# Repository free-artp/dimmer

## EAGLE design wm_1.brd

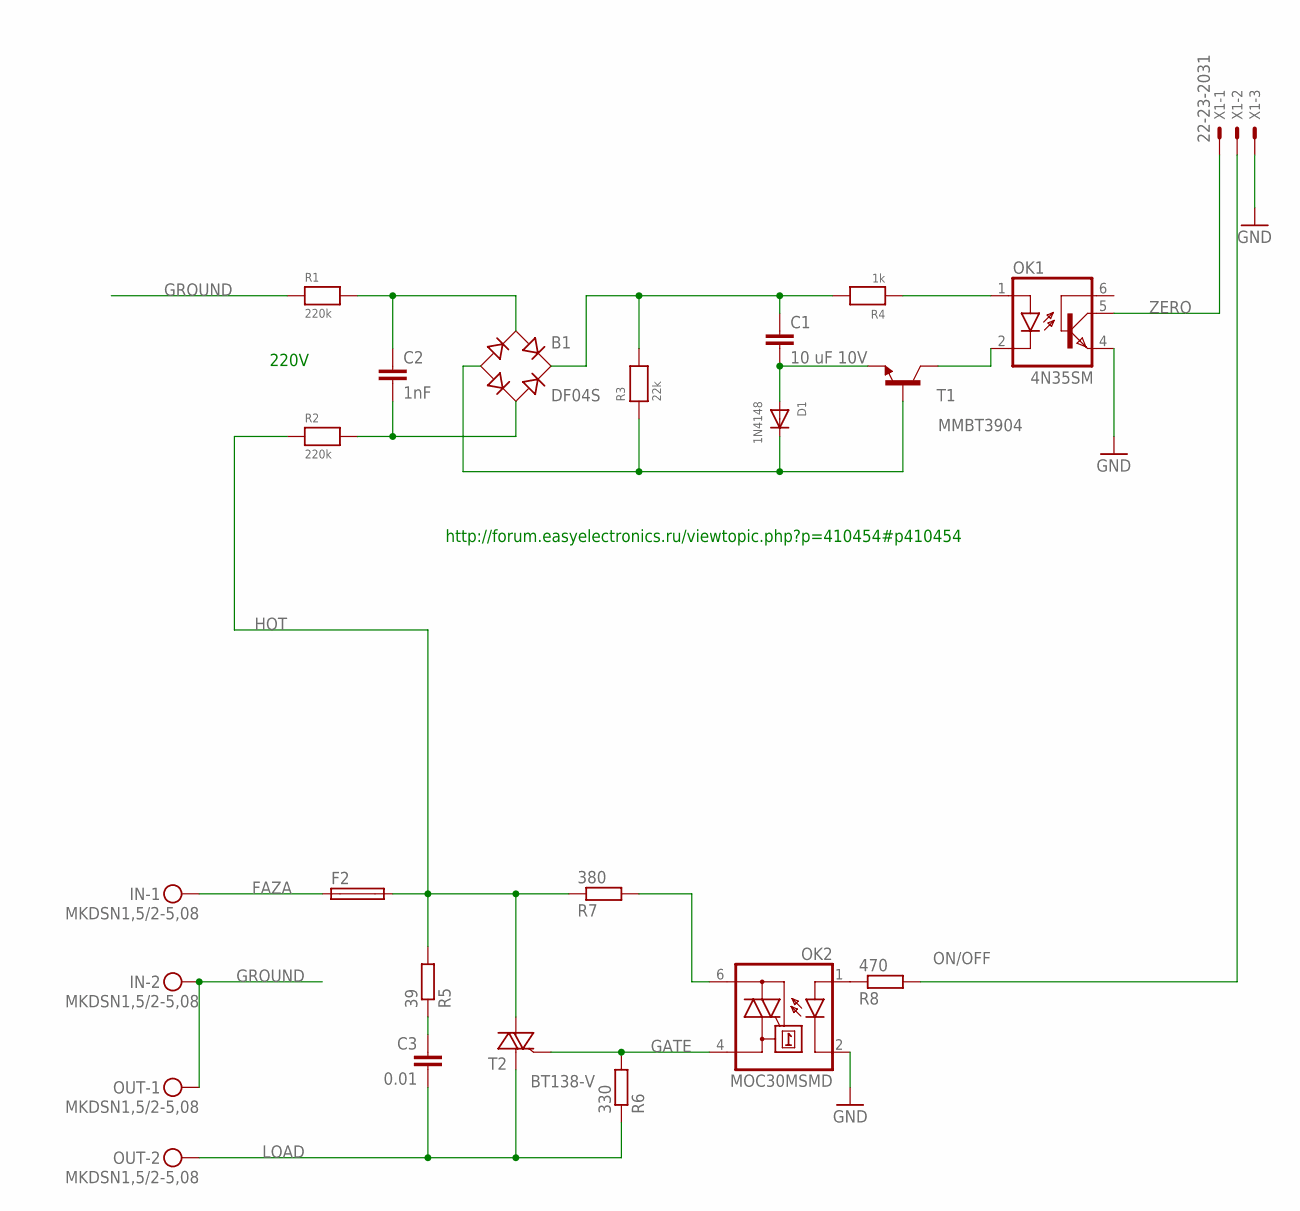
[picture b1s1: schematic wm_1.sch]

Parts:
B1: DF04S; DFS
C1: 10 uF 10V; C1206
C2: 1nF; C1206
C3: 0.01; C1206
D1: 1N4148; SOD-123
F2: SH22,5A
IN: MKDSN1,5/2-5,08
OK1: 4N35SM; DIL6-SMD
OK2: MOC30MSMD; DIL6-SMD
OUT: MKDSN1,5/2-5,08
R1, R2: 220k; 1206
R3: 22k; 1206
R4: 1k; 1206
R5: 39; R1206
R6: 330; R1206
R7: 380; R1206
R8: 470; R1206
T1: MMBT3904; SOT23-BEC
T2: BT138-V; TO220BV
X1: 22-23-2031

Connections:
FAZA: F2.1, IN.1
GATE: OK2.4 (A1), R6.2, T2.G
GND: OK1.4 (EMI), OK2.2 (C), X1.3
GROUND: IN.2, OUT.1, R1.1
HOT: F2.2, R2.1, R5.2, R7.1, T2.T2 (A2)
LOAD: C3.2, OUT.2, R6.1, T2.T1 (A1)
unnamed: B1.AC1, C2.1, R1.2
unnamed: B1.AC2, C2.2, R2.2
unnamed: C1.2, D1.A, T1.E
unnamed: B1.-, D1.C, R3.1, T1.B
unnamed: B1.+, C1.1, R3.2, R4.2
unnamed: OK1.1 (A), R4.1
unnamed: OK1.2 (C), T1.C
unnamed: C3.1, R5.1
unnamed: OK2.6 (A2), R7.2
unnamed: OK2.1 (A), R8.1
ON/OFF: R8.2, X1.2
ZERO: OK1.5 (COL), X1.1

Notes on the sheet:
http://forum.easyelectronics.ru/viewtopic.php?p=410454#p410454
220V

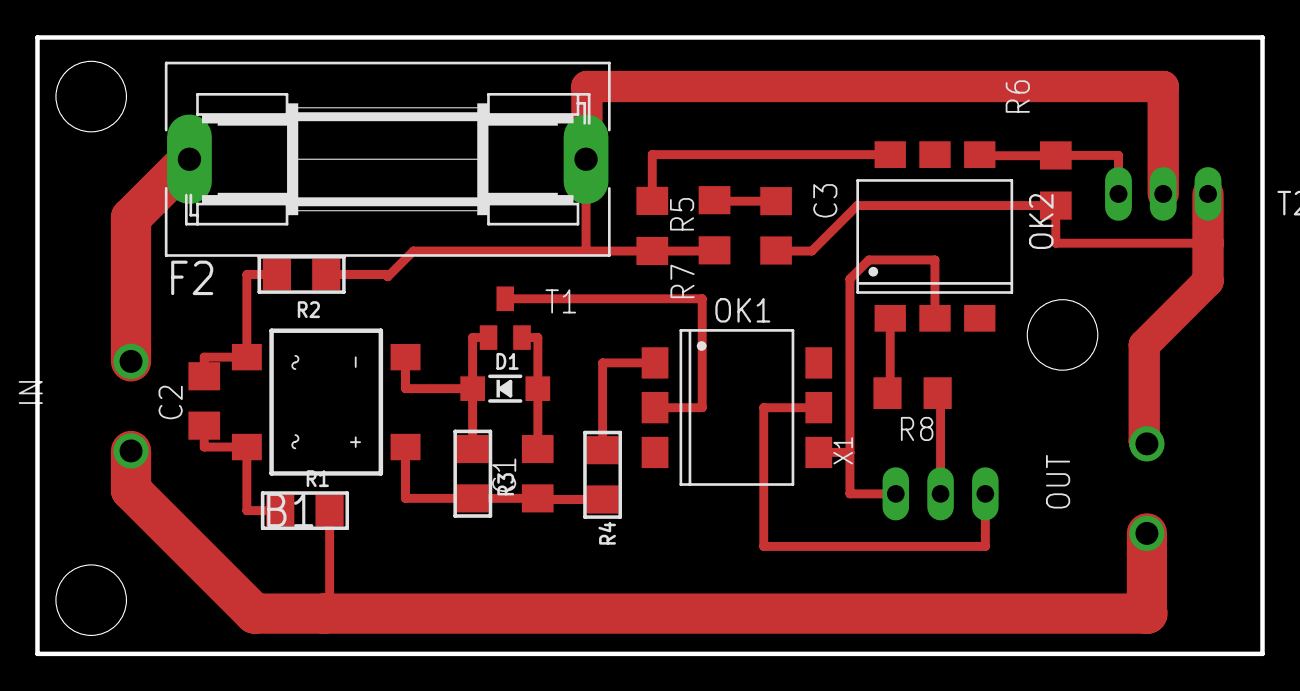
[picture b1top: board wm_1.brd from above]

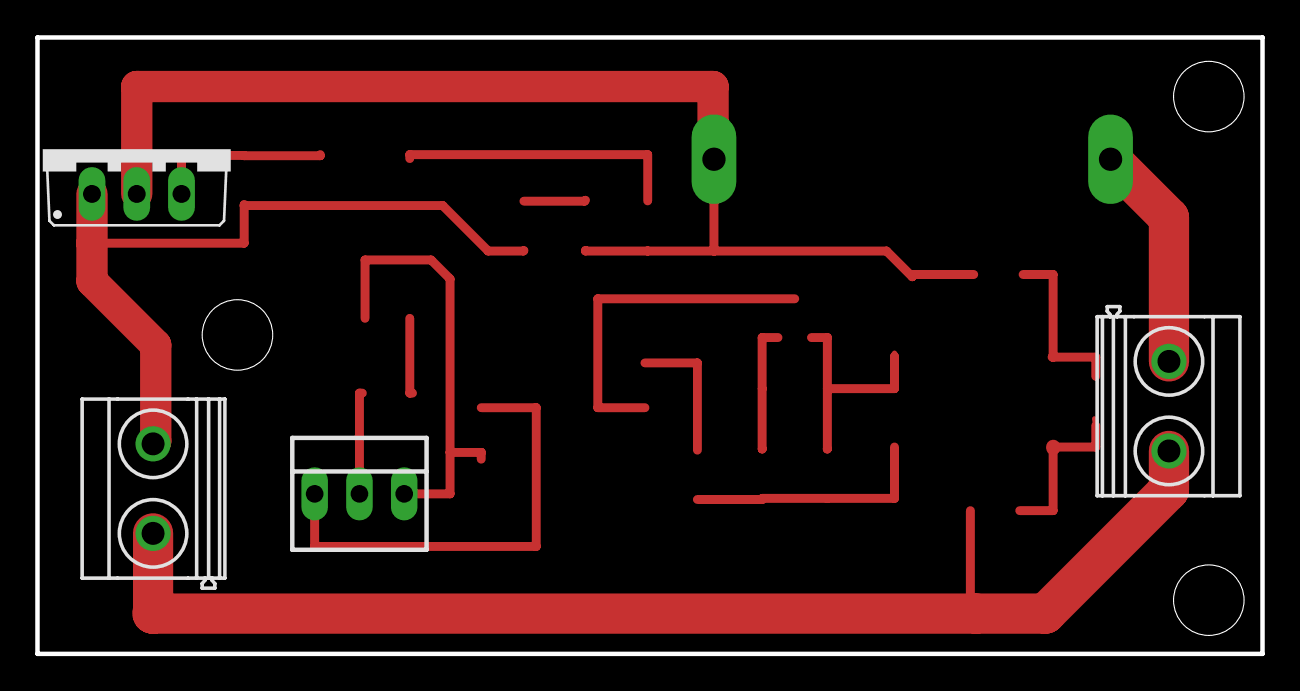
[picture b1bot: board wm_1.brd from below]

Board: 2 copper layers, 69.5 x 35.0 mm, 21 parts (4 on the bottom side), 18 nets.

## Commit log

2019-03-18 First pcb revision
2019-03-19 Заменил разъем и сделал линии 0.5мм
2019-04-02 first revision
2019-05-06 v2.1
2019-05-06 v2.2

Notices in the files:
parts and their libraries:
microbuilder: This work is placed in the public domain, and may be freely used for commercial and non-commercial work with the following conditions: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
